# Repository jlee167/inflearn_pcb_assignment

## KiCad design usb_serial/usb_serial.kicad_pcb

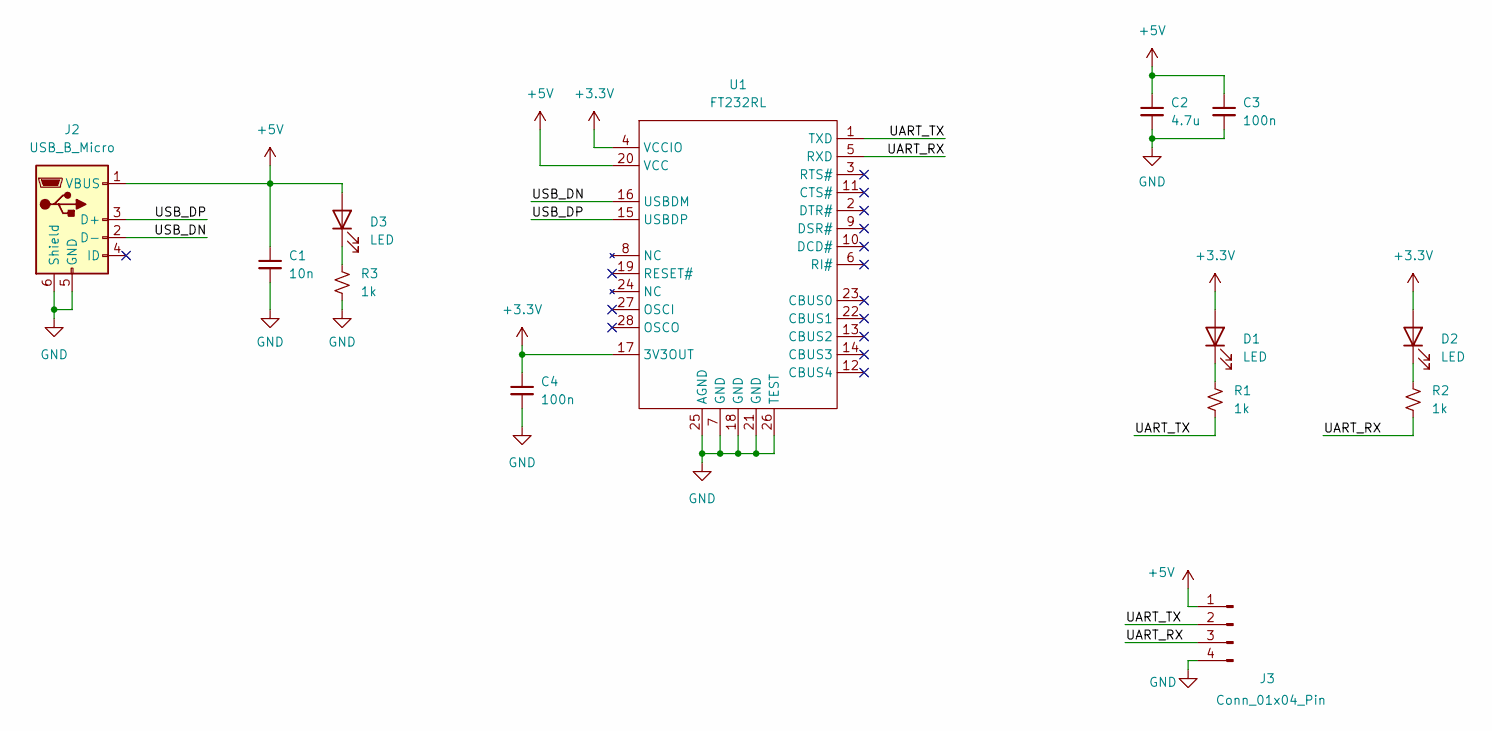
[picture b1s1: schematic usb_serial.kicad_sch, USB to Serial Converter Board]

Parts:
C1: 10n; C_0603_1608Metric; Part 0603B103K500NT; LCSC C57112
C2: 4.7u; C_0805_2012Metric; Part CL21A475KAQNNNE; LCSC C1779
C3, C4: 100n; C_0402_1005Metric; Part CL05B104KP5NNNC; LCSC C133086
D1, D2, D3: LED; LED_0805_2012Metric; Part ams-OSRAM USA INC.; LCSC C2899997
J2: USB_B_Micro; USB_Micro-B_Amphenol_10118194-0001LF_Horizontal; Part 10118194-0001LF; LCSC C132563
J3: Conn_01x04_Pin; PinHeader_1x04_P2.54mm_Vertical; Part 2.54-1*4P反弯排针; LCSC C91552
R1, R2, R3: 1k; R_0402_1005Metric; Part 0402WGF1001TCE; LCSC C11702
U1: FT232RL; 28-LD-SSOP; Part FT232RL; LCSC C8690

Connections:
+3.3V: C4.1, D1.2 (A), D2.2 (A), U1.4 (VCCIO), U1.17 (3V3OUT)
+5V: C1.1, C2.1, C3.1, D3.2 (A), J2.1 (VBUS), J3.1, U1.20 (VCC)
/UART_RX: J3.3, R2.1, U1.5 (RXD)
/UART_TX: J3.2, R1.1, U1.1 (TXD)
/USB_DN: J2.2 (D-), U1.16 (USBDM)
/USB_DP: J2.3 (D+), U1.15 (USBDP)
GND: C1.2, C2.2, C3.2, C4.2, J2.5 (GND), J2.6 (Shield), J3.4, R3.1, U1.7 (GND), U1.18 (GND), U1.21 (GND), U1.25 (AGND), U1.26 (TEST)
unnamed: D1.1 (K), R1.2
unnamed: D2.1 (K), R2.2
unnamed: D3.1 (K), R3.2

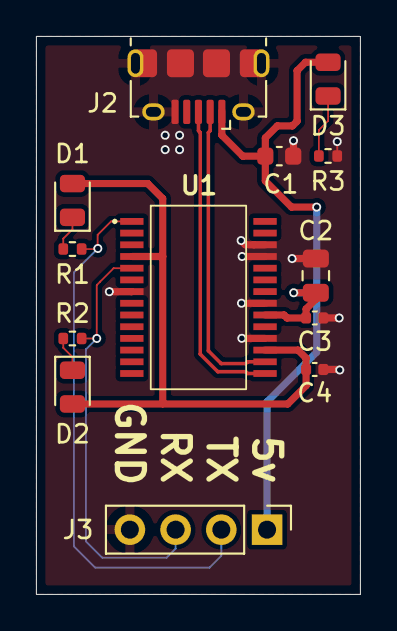
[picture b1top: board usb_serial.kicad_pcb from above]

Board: 2 copper layers, 18.0 x 31.0 mm, 13 parts (0 on the bottom side), 10 nets.

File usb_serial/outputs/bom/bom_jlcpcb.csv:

Designator,Comment,Footprint,LCSC
C1,10n,Capacitor_SMD:C_0603_1608Metric,C57112
C2,4.7u,Capacitor_SMD:C_0805_2012Metric,C1779
"C3,C4",100n,Capacitor_SMD:C_0402_1005Metric,C133086
"D1,D2,D3",LED,LED_SMD:LED_0805_2012Metric,C2899997
J2,USB_B_Micro,Connector_USB:USB_Micro-B_Amphenol_10118194-0001LF_Horizontal,C132563
J3,Conn_01x04_Pin,Connector_PinHeader_2.54mm:PinHeader_1x04_P2.54mm_Vertical,C91552
"R1,R2,R3",1k,Resistor_SMD:R_0402_1005Metric,C11702
U1,FT232RL,user_footprints:28-LD-SSOP,C8690

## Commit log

2025-02-15 gitignore updated
2025-02-15 Project scaffolding + FT232RL symbol
2025-02-15 FT232RL Footprint Added
2025-02-15 Symbol/Footprint/3D linked together
2025-02-15 Mechanical Layer added to footprint
2025-02-15 Imported USB connector symbol/footprint/step
2025-02-15 Instantiated major components
2025-02-15 Power+Decoupling
2025-02-15 Schematic complete
2025-02-15 Board outline defined
2025-02-15 FT232RL Courtyard defined
2025-02-15 Placement done
2025-02-15 Cooper fill + USB connector footprint change
2025-02-15 Routing done
2025-02-15 Set rules + DRC
2025-02-15 Realigned schematic
2025-02-15 Gerber generated
2025-02-15 BOM generated
2025-02-15 Centroid file generated
2025-02-15 Schematics generated
2025-02-15 BOM Fix - wrong reg value
2025-02-15 JLCPCB adaptation - USB part changed
2025-02-15 JLCPCB Ready - bom/Gerber/PnP/Schematic regenerated
2025-02-16 Layout fix - Stub removal
2025-02-23 [Feat] Added 3D model for new USB connector
2025-02-23 Silk screen realigned
2025-02-23 Gerbr & PnP regenerated
2025-02-23 Mechanical Diagram added
2025-03-28 [FIX] Changed 4pin 2.54mm header from vertical one to a right-angled one
2025-03-29 Updated Legend
2025-04-12 Added missing Gerber and Centroid
